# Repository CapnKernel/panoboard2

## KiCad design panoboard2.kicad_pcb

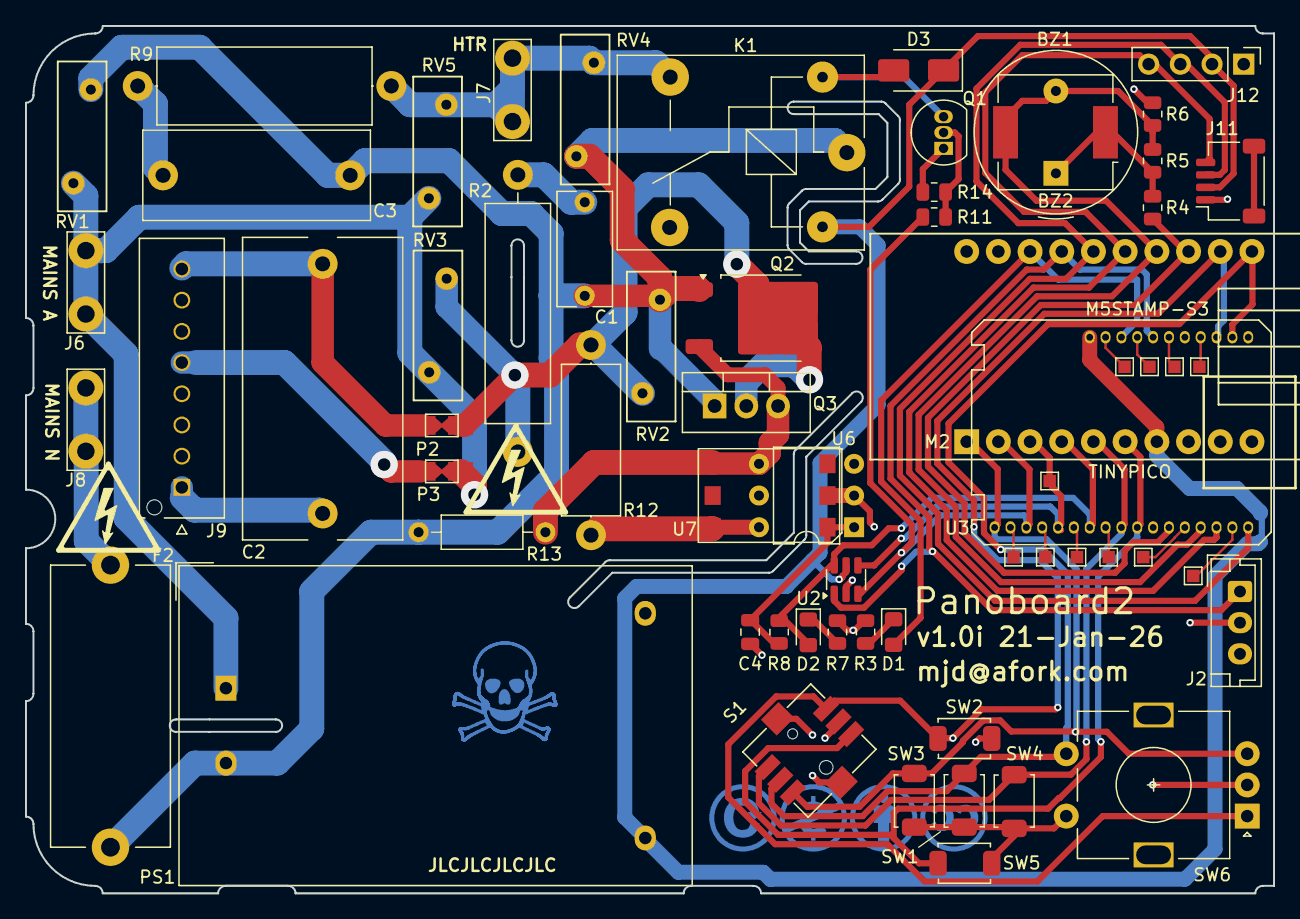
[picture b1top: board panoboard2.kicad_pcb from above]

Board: 2 copper layers, 100.0 x 69.5 mm, 64 parts (0 on the bottom side), 44 nets.

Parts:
BZ1: Buzzer; Buzzer_D12mm_H8.1mm
BZ2: FUET9018; Buzzer_CUI_CPT-9019S-SMT
C1: 100n 250V; C_Rect_L9.0mm_W4.2mm_P7.50mm_MKT
C2: 3uF 430VAC; C_Rect_L24.0mm_W12.6mm_P20.00mm_MKT
C3: 10n 1000V; C_Rect_L18.0mm_W7.0mm_P15.00mm_FKS3_FKP3
C4: 10n; C_0805_2012Metric
D1, D2: R LED; LED_0805_2012Metric_Pad1.15x1.40mm_HandSolder
D3: SS34; D_SMA
F2: 5A; Fuseholder_Cylinder-5x20mm_Stelvio-Kontek_PTF78_Horizontal_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
J2: THERMISTOR; JST_EH_B3B-EH-A_1x03_P2.50mm_Vertical
J6: BLK/MAINS L; TE-1742361-1-QC-Tab
J7: WHT/HTR; TE-1742361-1-QC-Tab
J8: ORA/MAINS N; TE-1742361-1-QC-Tab
J9: MOLEX 53375-0810; MOLEX_533750810
J11: I2C1; JST_SH_SM04B-SRSS-TB_1x04-1MP_P1.00mm_Horizontal
J12: I2C2; PinHeader_1x04_P2.54mm_Vertical
JP1, JP22, JP23, JP24, JP25, JP29, JP30, JP31, JP32, JP33, JP34: PCB_Pin_Breakout; TestPoint_Pad_1.0x1.0mm
K1: Relay_SPDT; Relay_SPDT_SANYOU_SRD_Series_Form_C
M2: TINYPICO
P2, P3: PCB_Patch; SolderJumper-2_P1.3mm_Bridged_Pad1.0x1.5mm
PS1: HLK-5M03; Converter_ACDC_Hi-Link_HLK-5Mxx
Q1: 2N7000; TO-92_Inline
Q2: BT136S-600; TO-252-2
Q3: BT136-600; TO-220-3_Vertical
R2: 22R 2W; R_Axial_DIN0516_L15.5mm_D5.0mm_P22.2mm_Horizontal
R3: R; R_0805_2012Metric
R4, R5: 1k; R_0805_2012Metric
R6: 100k; R_0805_2012Metric
R7: R so I=5mA; R_0805_2012Metric
R8: R so I=10mA; R_0805_2012Metric
R9: 39R 2W; R_Axial_DIN0617_L17.0mm_D6.0mm_P20.32mm_Horizontal
R11: 220R; R_0805_2012Metric
R12: 360R 1W; R_Axial_DIN0414_L11.9mm_D4.5mm_P15.24mm_Horizontal
R13: 360R; R_Axial_DIN0207_L6.3mm_D2.5mm_P10.16mm_Horizontal
R14: 10k; R_0805_2012Metric
RV1, RV2, RV3, RV4, RV5: 10D271K; RV_Disc_D12mm_W3.9mm_P7.5mm
S1: SKRHABE010
SW1, SW2, SW3, SW4, SW5: SW_Push; SW_Push_SPST_NO_432
SW6: RotaryEncoder_Switch_MP; RotaryEncoder_Alps_EC11E-Switch_Vertical_H20mm
U2: SRV05-4; SOT-23-6
U3: M5STAMP-S3; STAMP-S3-DIP_copy
U6: MOC3063; DIP-6_W7.62mm
U7: MOC3063S; SOIC-6

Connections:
+3V3: D3.1 (K), J11.2, J12.2, K1.A1, M2.7 (V3.3), PS1.4 (+Vout), U2.5 (VP), U3.28 (3V3)
/BUZZ1: M2.13 (18), R4.2, U3.12 (A2CH0/TCH11/GPIO11)
/BUZZ2: BZ1.2 (-), BZ2.2 (-), M2.14 (5), R5.1, R6.2, U3.14 (A2CH1/TCH12/GPIO12)
/DS18B20: JP1.1, M2.3 (27), U2.4 (IO3), U3.5 (A1CH4/TCH5/GPIO5)
/HEATER: M2.2 (26), R11.1, U2.3 (IO2), U3.3 (A1CH2/TCH3/GPIO3)
/HTR_N: J7.1, K1.14, R9.1, RV4.2, RV5.2
/LED: D1.2 (A), M2.18 (33), U3.26 (GPIO43/CLK1/TXD)
/MOTOR: D2.2 (A), M2.4 (15), R8.1, U2.6 (IO4), U3.7 (A1CH6/TCH7/GPIO7)
/MTR_N: P2.1, Q2.2 (A2), Q3.2 (A2), R2.2, R12.1, RV2.2, RV3.2
/SCL: J11.4, J12.4, M2.15 (22), U3.15 (A2CH2/TCH13/GPIO13/SDA)
/SDA: J11.3, J12.3, M2.16 (21), U3.17 (A2CH4/TCH1/GPIO15/SCL)
/SW1: M2.11 (23), S1.2, SW1.1, SW6.S1, U3.19 (GPIO39/CLK3/MTCK)
/SW2: M2.12 (19), S1.4, SW2.2, SW6.A, U3.20 (GPIO0)
/SW3: M2.1 (25), S1.3, SW3.1, SW6.B, U3.1 (A1CH0/TCH1/GPIO1)
/SW4: M2.5 (14), S1.1, SW4.2, U3.9 (A1CH8/TCH9/GPIO9)
/SW5: M2.6 (4), S1.6, SW5.2, U3.10 (A1CH9/TCH10/GPIO10)
/THERM: J2.1, M2.17 (32), U2.1 (IO1), U3.24 (GPIO44/CLK2/RXD)
GND: C4.2, J2.2, J2.3, J11.1, J12.1, M2.9 (GND), PS1.3 (-Vout), Q1.1 (S), R3.2, R6.1, R7.1, R14.1, S1.5, S1.SH1, S1.SH2, SW1.2, SW2.1, SW3.2, SW4.1, SW5.1, SW6.C, SW6.MP, SW6.S2, U2.2 (VN), U3.11 (GND), U3.18 (GND), U6.2, U7.2
MAINS_A: J6.1, P3.1, PS1.1 (AC/L), RV1.1, RV3.1, RV5.1
MAINS_N: C1.1, C3.2, F2.2, K1.11, PS1.2 (AC/N), Q2.1 (A1), Q3.1 (A1), R13.2, RV1.2, RV2.1, RV4.1
unnamed: BZ1.1 (+), BZ2.1 (+), R4.1, R5.2
unnamed: C1.2, R2.1
unnamed: C3.1, R9.2
unnamed: C4.1, R8.2, U6.1, U7.1
unnamed: D1.1 (K), R3.1
unnamed: D2.1 (K), R7.2
unnamed: D3.2 (A), K1.A2, Q1.3 (D)
unnamed: F2.1, J8.1
unnamed: C2.1, J9.1
unnamed: J9.5, P3.2
unnamed: C2.2, J9.8, P2.2
unnamed: Q1.2 (G), R11.2, R14.2
unnamed: Q2.3 (G), Q3.3 (G), R13.1, U6.4, U7.4
unnamed: R12.2, U6.6, U7.6
unnamed: JP30.1, U3.13 (5V)
unnamed: JP22.1, U3.2 (A1CH1/TCH2/GPIO2)
unnamed: JP23.1, U3.4 (A1CH3/TCH4/GPIO4)
unnamed: JP24.1, U3.6 (A1CH5/TCH6/GPIO6)
unnamed: JP25.1, U3.8 (A1CH7/TCH8/GPIO8)
unnamed: JP29.1, U3.16 (A2CH3/TCH14/GPIO14)
unnamed: JP34.1, U3.21 (GPIO40/CLK2/MTD0)
unnamed: JP33.1, U3.23 (GPIO41/CLK1/MTDI)
unnamed: JP32.1, U3.25 (GPIO42/MTMS)
unnamed: JP31.1, U3.27 (GPIO46)

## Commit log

2024-05-31 First revision
2024-06-19 More mods
2024-07-10 Revision 1.0c, after fit tests
2024-07-10 Many improvements
    Moved fuse to the neutral line so heater is protected
    Added slot under R2
    Moved mounting hole
    Improved board outline
    Added OSHW licence and KiCad shout-out
    Fixed buzzer pin pitch
2024-07-11 Removed a rebate because there's a support under it.
2024-07-11 Moved soldermask no-mans-land to match new slots.
2024-07-11 Added JLC production code placement cue
2024-07-13 Rotated incorrectly placed motor connector, and added many 3D models.
2026-01-21 Added LCSC part number for 2N7000
2026-01-21 Ignore a bunch of files
2026-01-21 Saved with KiCad 9
2026-01-21 Added footprint in use but not yet committed.
2026-01-21 Added a notes file
2026-01-21 Fixed location and size of fuse 3d model
2026-01-21 Bumped version number
2026-01-21 Ignore gerber and drill files

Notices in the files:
panoboard2.kicad_pcb:
CC BY-NC-SA 4.0
